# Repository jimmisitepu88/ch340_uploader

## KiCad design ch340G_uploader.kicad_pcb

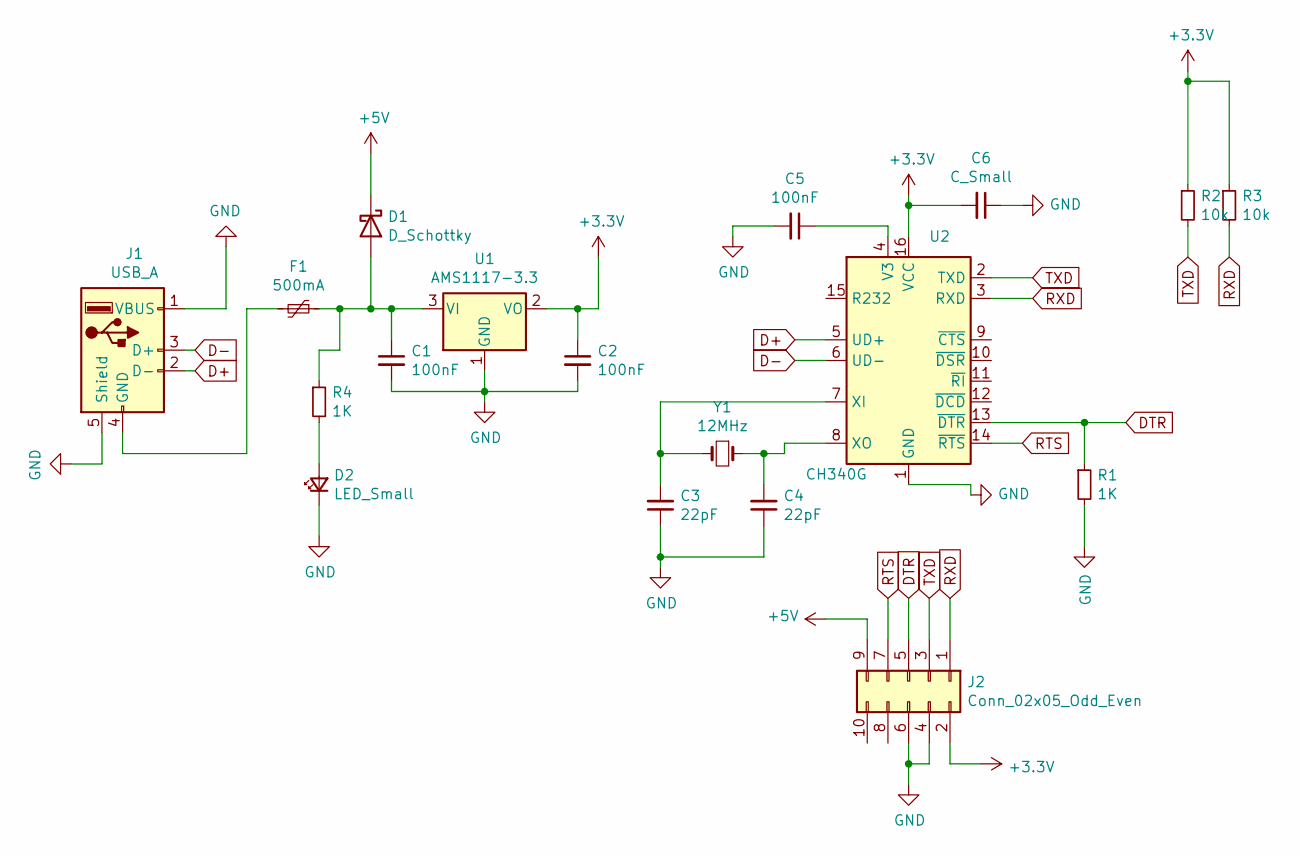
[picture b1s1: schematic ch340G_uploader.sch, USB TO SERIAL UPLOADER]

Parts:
C1, C2, C5: 100nF; C0805
C3, C4: 22pF; C0805
C6: C_Small; C0805
D1: D_Schottky; D_SOD-128
D2: LED_Small; LED_0805_2012Metric_Pad1.15x1.40mm_HandSolder
F1: 500mA; Fuse_1206_3216Metric
J1: USB_A; USB_A_Stewart_SS-52100-001_Horizontal
J2: Conn_02x05_Odd_Even; PinHeader_2x05_P2.54mm_Vertical
R1, R4: 1K; R0805_rev
R2, R3: 10k; R0805_rev
U1: AMS1117-3.3; SOT-223-3_TabPin2
U2: CH340G; SOIC-16_3.9x9.9mm_P1.27mm
Y1: 12MHz; Crystal_SMD_HC49-SD

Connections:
+3V3: C2.1, C6.2, J2.2, R2.1, R3.1, U1.2 (VO), U2.16 (VCC)
+5V: D1.1 (K), J2.9
D+: J1.2 (D-), U2.5 (UD+)
D-: J1.3 (D+), U2.6 (UD-)
DTR: J2.5, R1.1, U2.13 (~DTR)
GND: C1.2, C2.2, C3.1, C4.1, C5.2, C6.1, D2.1 (K), J1.1 (VBUS), J1.5 (Shield), J2.4, J2.6, R1.2, U1.1 (GND), U2.1 (GND)
unnamed: C1.1, D1.2 (A), F1.1, R4.1, U1.3 (VI)
unnamed: C3.2, U2.7 (XI), Y1.2
unnamed: C4.2, U2.8 (XO), Y1.1
unnamed: C5.1, U2.4 (V3)
unnamed: D2.2 (A), R4.2
unnamed: F1.2, J1.4 (GND)
RTS: J2.7, U2.14 (~RTS)
RXD: J2.1, R3.2, U2.3 (RXD)
TXD: J2.3, R2.2, U2.2 (TXD)

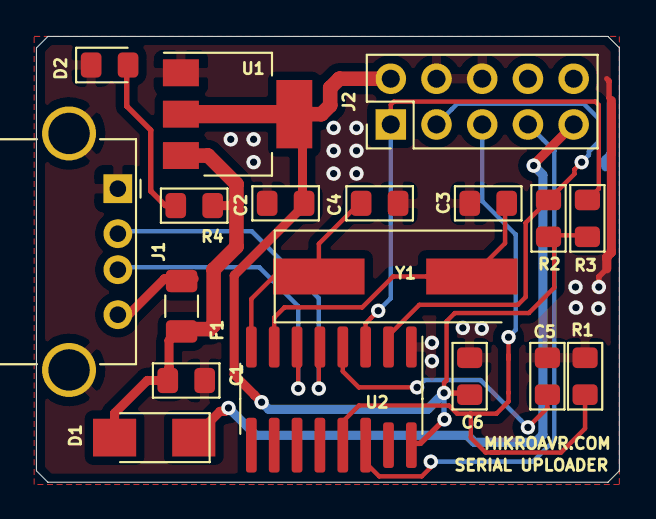
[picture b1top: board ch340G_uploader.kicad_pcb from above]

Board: 2 copper layers, 32.4 x 24.8 mm, 18 parts (0 on the bottom side), 15 nets.
